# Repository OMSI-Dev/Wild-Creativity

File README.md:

# Flea Electronics Details
## Theory of Operation
Basic gameplay is three targets that are activated by IR sensors. The IR sensor detects when a ball is passing through the hole and triggers a sound effect and a lighting effect. After all three targets are hit within the games time limit a win sequence is activated and a win sound triggers. The game goes dark for five seconds and begins the attractor sequence. 

## Updating software

The software is built using platform.io. You can use Arduino IDE by copying the src folder and renaming it to Helmet and renaming the main.cpp file to ‘Helmet.ino’. This will allow you to use Arduino to make modifications. You will need to install any missing libraries through the Arduino Library manager.

## Project File Organization

	docs : documentation and pictures
	src : source code
	eagle : pcb files
	examples_tests : N/A
	readme.md : basic project info its the file you are reading
	resources:Flea BOM.xls
	
	some other directories are used by platformio and vscode

#### Hardware

**Phoenix connectors:**

2-pin: (4 qty)

3-pin: (3 qty)

4-pin: (2 qty)

6-pin: (1 qty)

Various Components:

    1.WS2811 daisychain lights
    2.5V PSU
    3.IR sensors

## Audio
A WAV trigger is used and controlled via serial communication. Audio files are saved as 16-bit WAV files on the installed SD card.

The audio uses a naming convention of 001_Win.WAV

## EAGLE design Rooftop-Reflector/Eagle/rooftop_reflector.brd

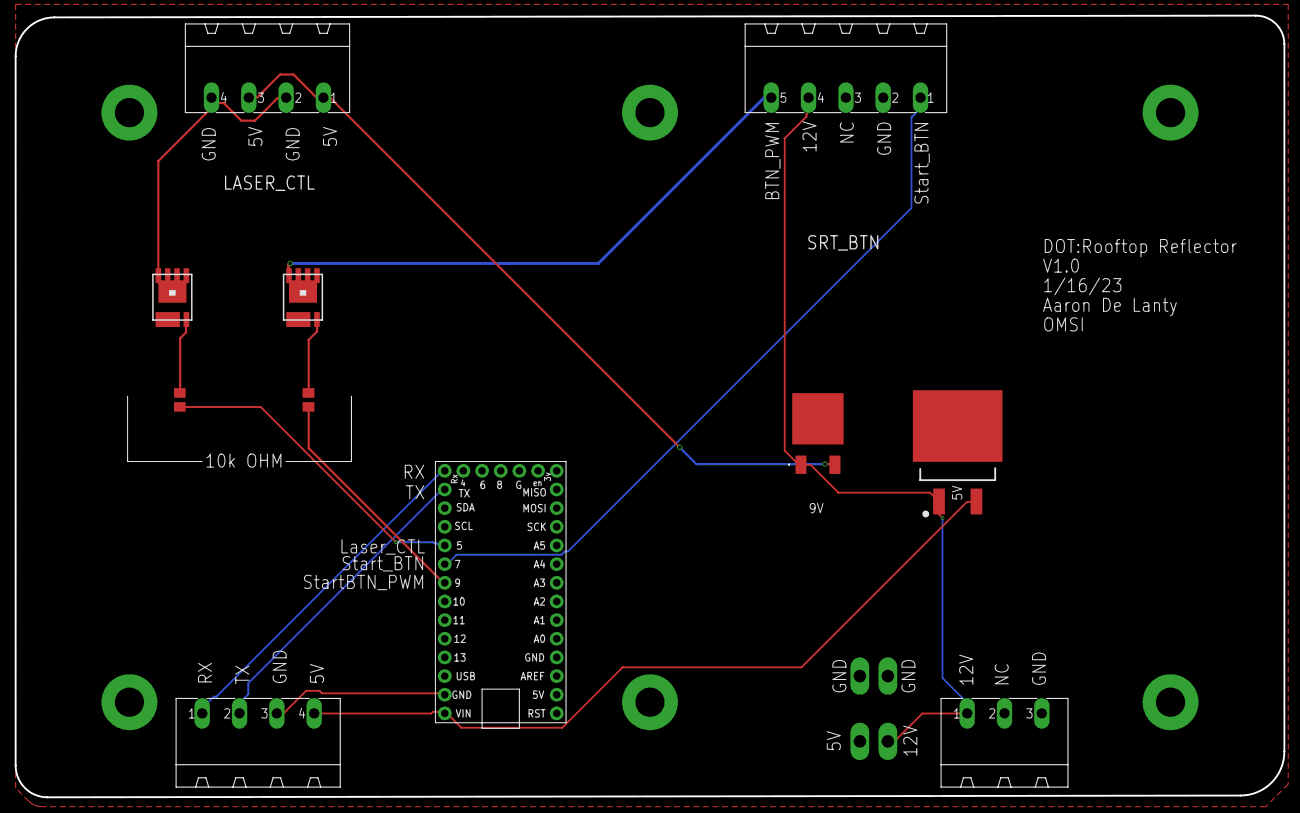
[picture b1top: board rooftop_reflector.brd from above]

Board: 2 copper layers, 172.7 x 106.4 mm, 19 parts (0 on the bottom side), 14 nets.

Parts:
5V: L7805ABD2T-TR; D2PAK-STB35NF10T4
9V: BA17809FP-E2; BA17809FPE2
10K1, 10K3: M0805
12VIN: MSTBA3
LASER_CTL: MSTBA4
Q1, Q4: MOSFET-NCH; SO-8_POWER_PAK
S1, S2, S3, S4, S6, S8: STANDOFF_ELECTRICAL5-32; STANDOFF_ELECTRICAL_5_32
SRT_BTN: MSTBA5
TP1, TP2: PTR2; P2-38-17
U1: ADAFRUIT_LEONARDO; ADAFRUIT_LENOARDO
X1: MSTBA4

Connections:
5V: 5V.3, U1.VIN, X1.4
9V: 9V.3, LASER_CTL.1, LASER_CTL.3
12V: 5V.1, 9V.1, 12VIN.1, SRT_BTN.4, TP2.TP-1
D5: 10K1.2, U1.D5
D9: 10K3.2, U1.D9
GND: 5V.4, 9V.2, 12VIN.3, Q1.S, Q4.S, S1.P1, S2.P1, S3.P1, S4.P1, S6.P1, S8.P1, SRT_BTN.2, TP1.TP-1, U1.GND@0
LZR_CTL: LASER_CTL.2, LASER_CTL.4, Q1.D1
unnamed: SRT_BTN.1, U1.D7
unnamed: 10K1.1, Q1.G
unnamed: U1.TX, X1.2
unnamed: U1.RX, X1.1
unnamed: U1.GND@2, X1.3
unnamed: 10K3.1, Q4.G
SRT_PWM: Q4.D1, SRT_BTN.5

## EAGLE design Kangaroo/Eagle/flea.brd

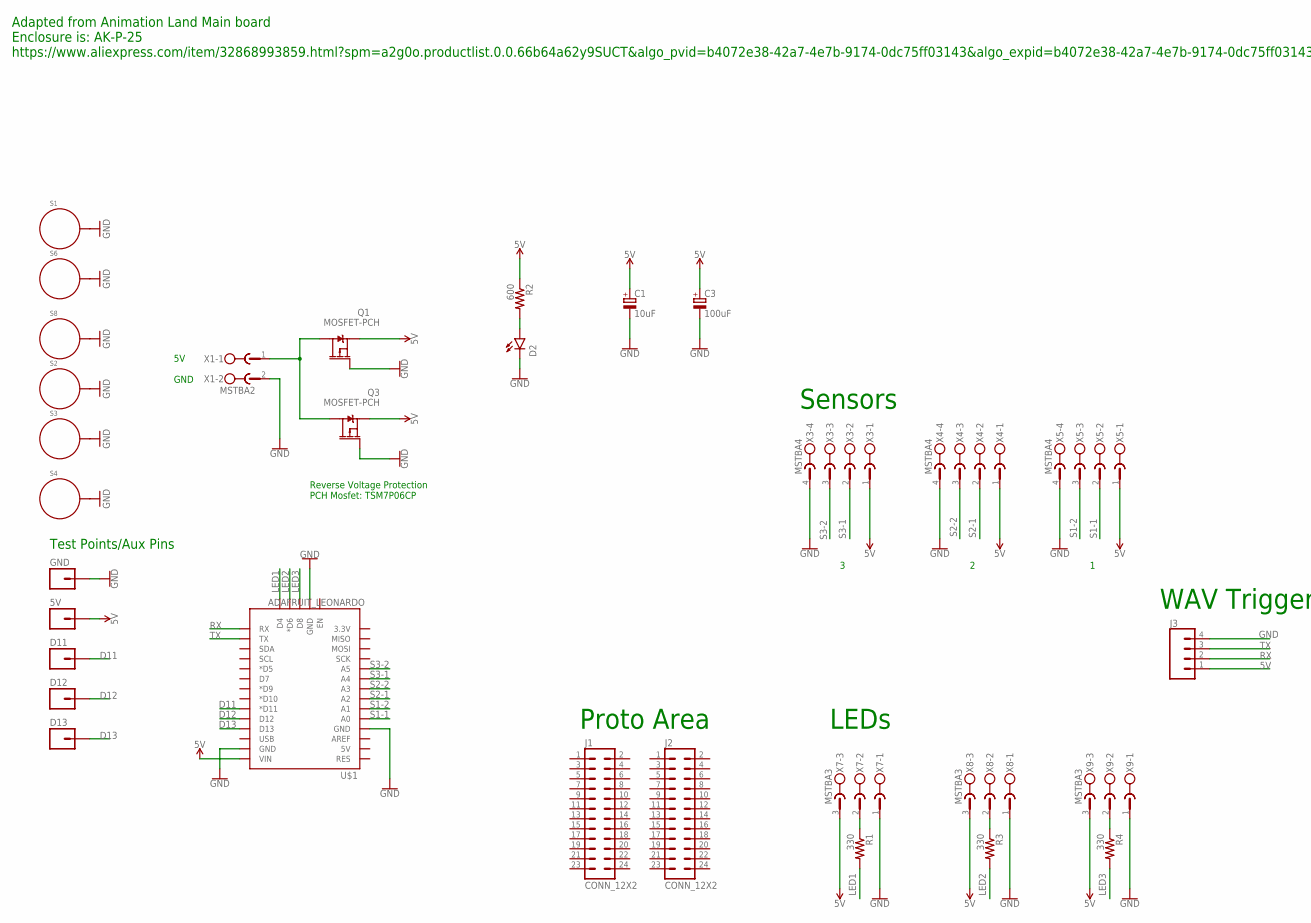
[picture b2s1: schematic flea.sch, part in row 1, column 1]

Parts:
5V: M01PTH; 1X01
C1: 10uF; E2-5
C3: 100uF; E3,5-10
D2: RED; SPARKFUN-LED_LED-1206
D11, D12, D13: M01PTH; 1X01
GND: M01PTH; 1X01
J1, J2: CONN_12X2; 2X12
J3: CONN_043.5MM_RA; 1X04_3.5MM_RA
Q1, Q3: MOSFET-PCH; DPAK
R1, R3, R4: 330; R0805
R2: 600; R0805
S1, S2, S3, S4, S6, S8: STANDOFF_ELECTRICAL5-32; STANDOFF_ELECTRICAL_5_32
U$1: ADAFRUIT_LEONARDO; ADAFRUIT_LENOARDO
X1: MSTBA2
X3, X4, X5: MSTBA4
X7, X8, X9: MSTBA3

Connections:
5V: 5V.1, C1.+, C3.+, J3.1, Q1.3 (S), Q3.3 (S), R2.1, U$1.VIN, X3.1, X4.1, X5.1, X7.3, X8.3, X9.3
D11: D11.1, U$1.D11 (*D11)
D12: D12.1, U$1.D12
D13: D13.1, U$1.D13
GND: C1.-, C3.-, D2.C, GND.1, J3.4, Q1.1 (G), Q3.1 (G), S1.P1, S2.P1, S3.P1, S4.P1, S6.P1, S8.P1, U$1.GND@0 (GND), U$1.GND@1 (GND), U$1.GND@2 (GND), X1.2, X3.4, X4.4, X5.4, X7.1, X8.1, X9.1
LED1: R1.2, U$1.D4
LED2: R3.2, U$1.D6 (*D6)
LED3: R4.2, U$1.D8
unnamed: D2.A, R2.2
unnamed: R1.1, X7.2
unnamed: R3.1, X8.2
unnamed: R4.1, X9.2
unnamed: Q1.4 (D), Q3.4 (D), X1.1
RX: J3.2, U$1.RX
S1-1: U$1.A0, X5.2
S1-2: U$1.A1, X5.3
S2-1: U$1.A2, X4.2
S2-2: U$1.A3, X4.3
S3-1: U$1.A4, X3.2
S3-2: U$1.A5, X3.3
TX: J3.3, U$1.TX

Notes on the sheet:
Adapted from Animation Land Main board Enclosure is: AK-P-25 https://www.aliexpress.com/item/32868993859.html?spm=a2g0o.productlist.0.0.66b64a62y9SUCT&algo_pvid=b4072e38-42a7-4e7b-9174-0dc75ff03143&algo_expid=b4072e38-42a7-4e7b-9174-0dc75ff03143-1&btsid=0ab6f82415815303906962744e020c&ws_ab_test=sea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
Reverse Voltage Protection PCH Mosfet: TSM7P06CP
5V GND
Proto Area
Test Points/Aux Pins
LEDs
Sensors
WAV Trigger

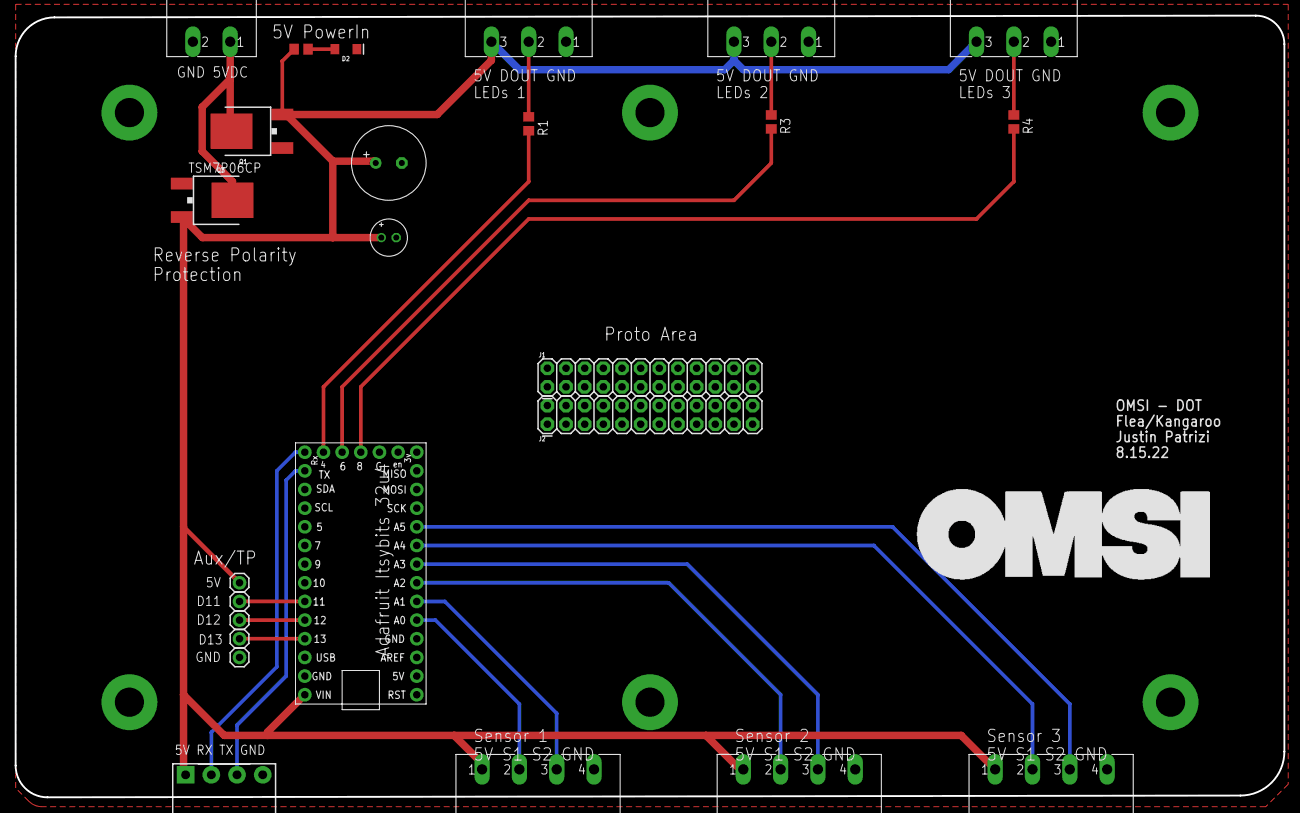
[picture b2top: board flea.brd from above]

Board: 2 copper layers, 172.7 x 106.4 mm, 31 parts (0 on the bottom side), 21 nets.

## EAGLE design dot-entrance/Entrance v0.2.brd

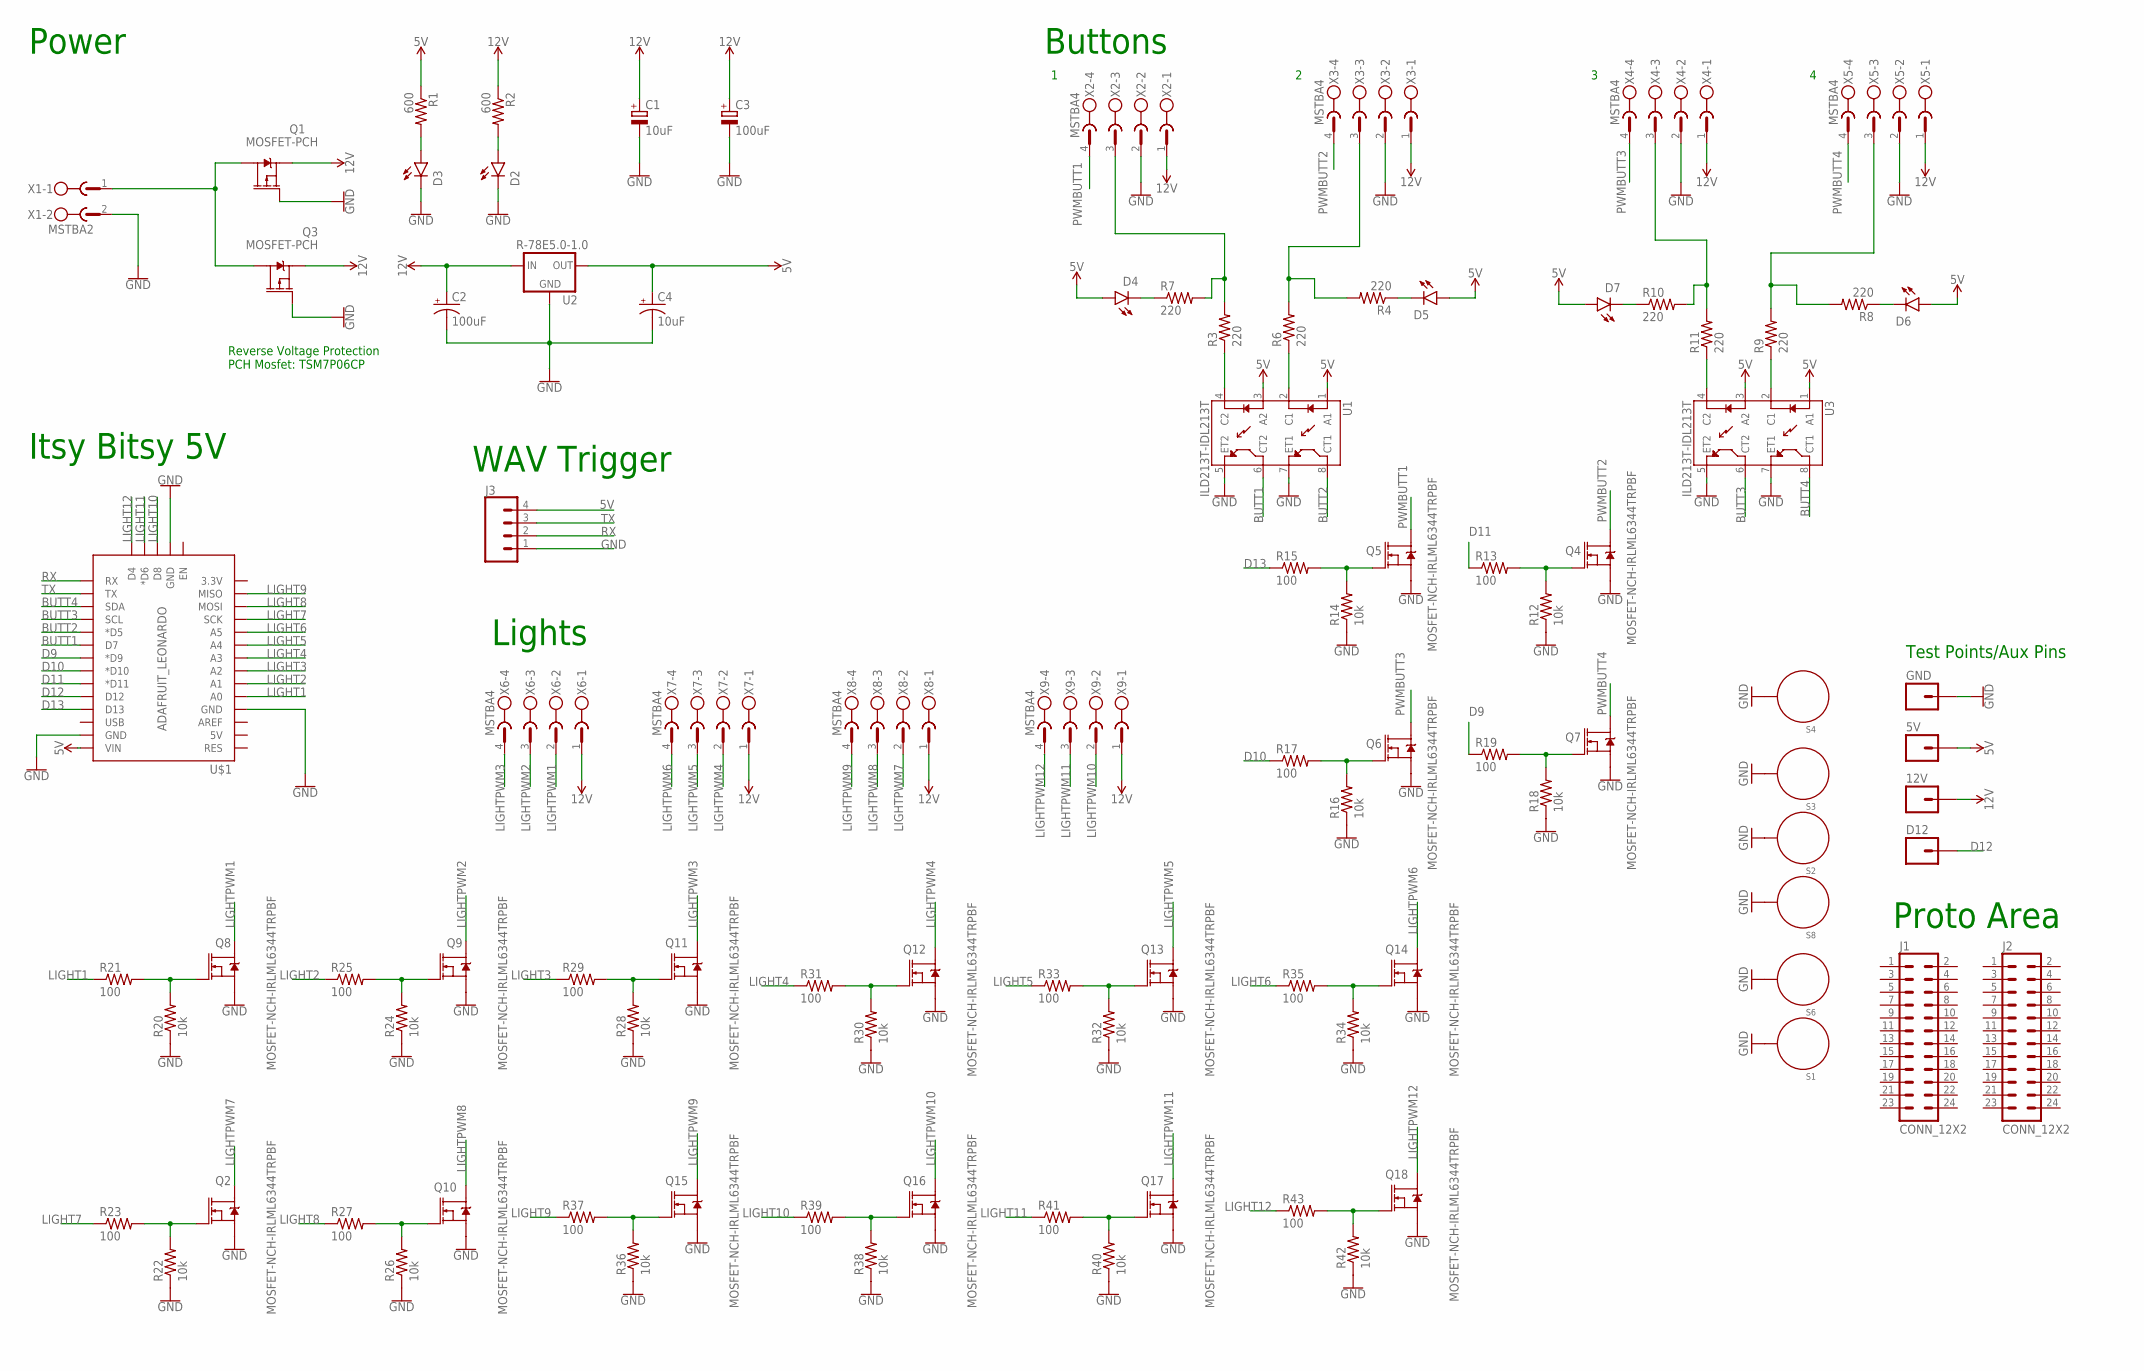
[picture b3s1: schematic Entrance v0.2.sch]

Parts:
5V, 12V: M01PTH; 1X01
C1: 10uF; E2-5
C2: 100uF; CPOL-RADIAL-2.5MM-6.5MM
C3: 100uF; E3,5-10
C4: 10uF; CPOL-RADIAL-2.5MM-5MM-KIT
D2, D3: RED; SPARKFUN-LED_LED-1206
D4, D5, D6, D7: RED; LED-1206
D12: M01PTH; 1X01
GND: M01PTH; 1X01
J1, J2: CONN_12X2; 2X12
J3: CONN_043.5MM_RA; 1X04_3.5MM_RA
Q1, Q3: MOSFET-PCH; DPAK@1
Q2, Q4, Q5, Q6, Q7, Q8, Q9, Q10, Q11, Q12, Q13, Q14, Q15, Q16, Q17, Q18: MOSFET-NCH-IRLML6344TRPBF; SOT23-3
R1, R2: 600; R0805
R3, R4, R6, R7, R8, R9, R10, R11: 220; R0805
R12, R14, R16, R18, R20, R22, R24, R26, R28, R30, R32, R34, R36, R38, R40, R42: 10k; R0805
R13, R15, R17, R19, R21, R23, R25, R27, R29, R31, R33, R35, R37, R39, R41, R43: 100; R0805
S1, S2, S3, S4, S6, S8: STANDOFF_ELECTRICAL5-32; STANDOFF_ELECTRICAL_5_32
U1, U3: ILD213T-IDL213T; SO08@1
U2: R-78E5.0-1.0; DC-DC_CONVERTER_78XX
U$1: ADAFRUIT_LEONARDO; ADAFRUIT_LENOARDO
X1: MSTBA2
X2, X3, X4, X5, X6, X7, X8, X9: MSTBA4

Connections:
5V: 5V.1, C4.1 (+), D4.A, D5.A, D6.A, D7.A, J3.4, R1.1, U1.1 (A1), U1.3 (A2), U2.VOUT (OUT), U3.1 (A1), U3.3 (A2), U$1.VIN
12V: 12V.1, C1.+, C2.1 (+), C3.+, Q1.3 (S), Q3.3 (S), R2.1, U2.VIN (IN), X2.1, X3.1, X4.1, X5.1, X6.1, X7.1, X8.1, X9.1
BUTT1: U1.6 (CT2), U$1.D7
BUTT2: U1.8 (CT1), U$1.D5 (*D5)
BUTT3: U3.6 (CT2), U$1.SCL
BUTT4: U3.8 (CT1), U$1.SDA
D9: R19.1, U$1.D9 (*D9)
D10: R17.1, U$1.D10 (*D10)
D11: R13.1, U$1.D11 (*D11)
D12: D12.1, U$1.D12
D13: R15.1, U$1.D13
GND: C1.-, C2.2 (-), C3.-, C4.2 (-), D2.C, D3.C, GND.1, J3.1, Q1.1 (G), Q2.2 (S), Q3.1 (G), Q4.2 (S), Q5.2 (S), Q6.2 (S), Q7.2 (S), Q8.2 (S), Q9.2 (S), Q10.2 (S), Q11.2 (S), Q12.2 (S), Q13.2 (S), Q14.2 (S), Q15.2 (S), Q16.2 (S), Q17.2 (S), Q18.2 (S), R12.1, R14.1, R16.1, R18.1, R20.1, R22.1, R24.1, R26.1, R28.1, R30.1, R32.1, R34.1, R36.1, R38.1, R40.1, R42.1, S1.P1, S2.P1, S3.P1, S4.P1, S6.P1, S8.P1, U1.5 (ET2), U1.7 (ET1), U2.GND, U3.5 (ET2), U3.7 (ET1), U$1.GND@0 (GND), U$1.GND@1 (GND), U$1.GND@2 (GND), X1.2, X2.2, X3.2, X4.2, X5.2
LIGHT1: R21.1, U$1.A0
LIGHT2: R25.1, U$1.A1
LIGHT3: R29.1, U$1.A2
LIGHT4: R31.1, U$1.A3
LIGHT5: R33.1, U$1.A4
LIGHT6: R35.1, U$1.A5
LIGHT7: R23.1, U$1.SCK
LIGHT8: R27.1, U$1.MOSI
LIGHT9: R37.1, U$1.MISO
LIGHT10: R39.1, U$1.D8
LIGHT11: R41.1, U$1.D6 (*D6)
LIGHT12: R43.1, U$1.D4
LIGHTPWM1: Q8.3 (D), X6.2
LIGHTPWM2: Q9.3 (D), X6.3
LIGHTPWM3: Q11.3 (D), X6.4
LIGHTPWM4: Q12.3 (D), X7.2
LIGHTPWM5: Q13.3 (D), X7.3
LIGHTPWM6: Q14.3 (D), X7.4
LIGHTPWM7: Q2.3 (D), X8.2
LIGHTPWM8: Q10.3 (D), X8.3
LIGHTPWM9: Q15.3 (D), X8.4
LIGHTPWM10: Q16.3 (D), X9.2
LIGHTPWM11: Q17.3 (D), X9.3
LIGHTPWM12: Q18.3 (D), X9.4
unnamed: R3.1, U1.4 (C2)
unnamed: D2.A, R2.2
unnamed: D6.C, R8.1
unnamed: D3.A, R1.2
unnamed: D4.C, R7.1
unnamed: D5.C, R4.1
unnamed: R3.2, R7.2, X2.3
unnamed: R6.1, U1.2 (C1)
unnamed: R4.2, R6.2, X3.3
unnamed: R9.1, U3.2 (C1)
unnamed: R8.2, R9.2, X5.3
unnamed: D7.C, R10.1
unnamed: R10.2, R11.2, X4.3
unnamed: R11.1, U3.4 (C2)
unnamed: Q5.1 (G), R14.2, R15.2
unnamed: Q6.1 (G), R16.2, R17.2
unnamed: Q7.1 (G), R18.2, R19.2
unnamed: Q1.4 (D), Q3.4 (D), X1.1
unnamed: Q8.1 (G), R20.2, R21.2
unnamed: Q2.1 (G), R22.2, R23.2
unnamed: Q9.1 (G), R24.2, R25.2
unnamed: Q10.1 (G), R26.2, R27.2
unnamed: Q11.1 (G), R28.2, R29.2
unnamed: Q4.1 (G), R12.2, R13.2
unnamed: Q12.1 (G), R30.2, R31.2
unnamed: Q13.1 (G), R32.2, R33.2
unnamed: Q14.1 (G), R34.2, R35.2
unnamed: Q15.1 (G), R36.2, R37.2
unnamed: Q16.1 (G), R38.2, R39.2
unnamed: Q17.1 (G), R40.2, R41.2
unnamed: Q18.1 (G), R42.2, R43.2
PWMBUTT1: Q5.3 (D), X2.4
PWMBUTT2: Q4.3 (D), X3.4
PWMBUTT3: Q6.3 (D), X4.4
PWMBUTT4: Q7.3 (D), X5.4
RX: J3.2, U$1.RX
TX: J3.3, U$1.TX

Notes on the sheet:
Reverse Voltage Protection PCH Mosfet: TSM7P06CP
Proto Area
Test Points/Aux Pins
Lights
Buttons
WAV Trigger
Itsy Bitsy 5V
Power

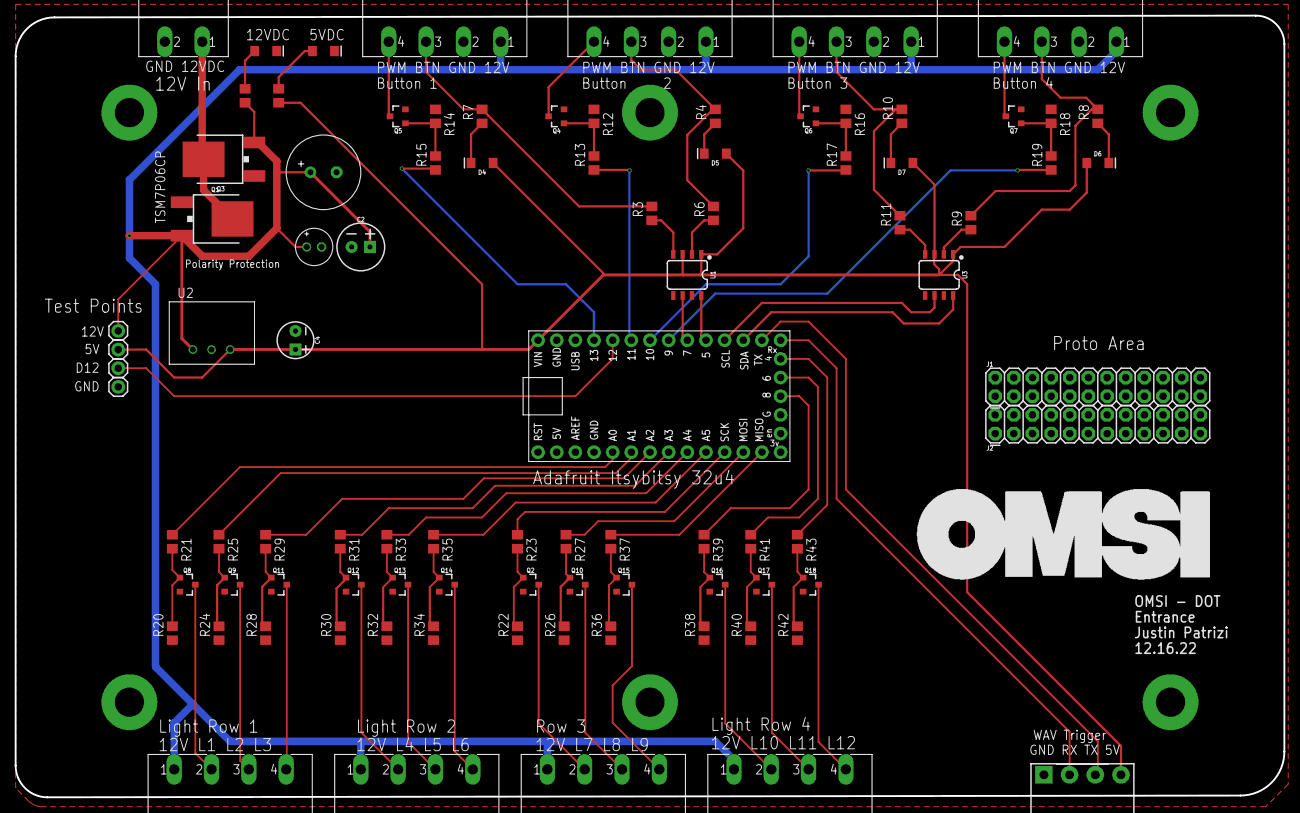
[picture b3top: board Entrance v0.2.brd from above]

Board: 2 copper layers, 172.7 x 106.4 mm, 96 parts (0 on the bottom side), 73 nets.

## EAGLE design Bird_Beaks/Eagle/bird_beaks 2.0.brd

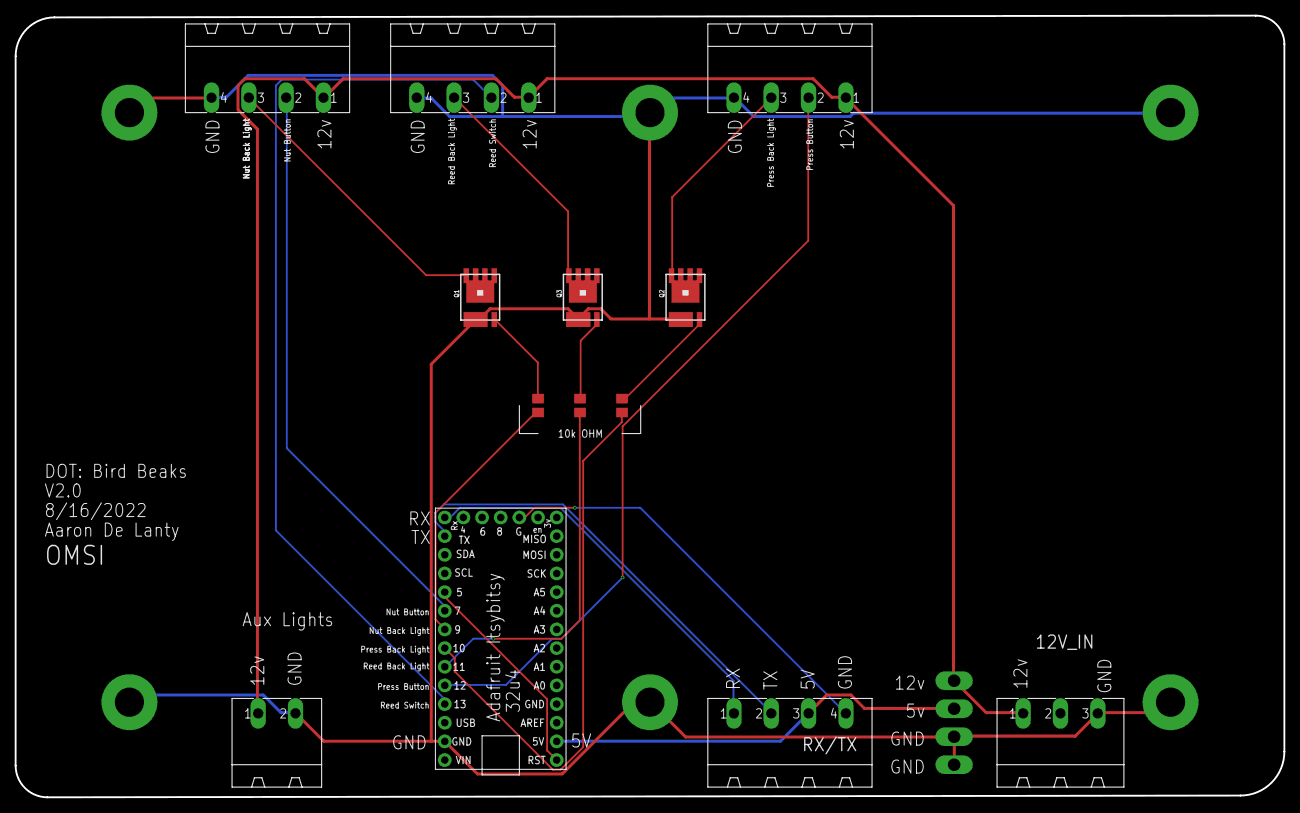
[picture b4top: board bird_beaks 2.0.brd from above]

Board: 2 copper layers, 172.7 x 106.4 mm, 21 parts (0 on the bottom side), 19 nets.

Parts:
10K, 10K1, 10K2: M0805
12V_IN: MSTBA3
Q1, Q2, Q3: MOSFET-NCH; SO-8_POWER_PAK
RX/TX: MSTBA4
S1, S2, S3, S4, S6, S8: STANDOFF_ELECTRICAL5-32; STANDOFF_ELECTRICAL_5_32
TP1, TP2: PTR2; P2-38-17
U1: ITSYBITSY_5V; ADAFRUIT_LENOARDO
X1, X2, X3: MSTBA4
X4: MSTBA2

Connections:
5V: RX/TX.3, TP2.TP-1, U1.5V
12V: 12V_IN.1, TP2.TP-2, X1.1, X2.1, X3.1, X4.1
D7: U1.D7, X1.2
D9: 10K.2, U1.D9
D10: 10K1.2, U1.D10
D11: 10K2.2, U1.D11
D12: U1.D12, X2.2
D13: U1.D13, X3.2
GND: 12V_IN.3, Q1.S, Q2.S, Q3.S, S1.P1, S2.P1, S3.P1, S4.P1, S6.P1, S8.P1, TP1.TP-1, TP1.TP-2, U1.GND@2, X1.4, X2.4, X3.4, X4.2
unnamed: 10K2.1, Q3.G
unnamed: 10K.1, Q1.G
unnamed: U1.D5, U1.RES
unnamed: Q1.D1, X1.3
unnamed: 10K1.1, Q2.G
unnamed: RX/TX.2, U1.TX
unnamed: Q2.D1, X2.3
unnamed: RX/TX.4, U1.GND@1
unnamed: RX/TX.1, U1.RX
unnamed: Q3.D1, X3.3

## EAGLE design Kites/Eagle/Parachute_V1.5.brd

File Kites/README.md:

# Kites Electronics Details
### Theory of Operation
The basic operation of kites is a processing sketch and a uController controlling two blower fans and reading a veneer force sensor. The uController has a start and stop button connected to control the gameplay game state. 

When the start button is pressed it sends a signal to processing to activate the data output screen. This then pulls down the signal to start the fans connected to the relay-controlled powerstrip. The uController reads the incoming sensor data and sends it over serial signal packets with an LF to end the packet. Processing takes the data and maps it to a -35 to 35 value that determines the position of the dial gauge's rotation on the screen. This data also updates the battery charging levels relative to the gauge. After the game timeout, it outputs a results screen that translates the gauge to the number of minutes to charge a battery. 

The processing app handles the game timing once it gets the signal from the uController to start the game. It will also cut the game off sooner if the stop button is pushed during gameplay. When it receives the signal to start it does a countdown to start the game while the fans spin up. The game plays for the duration of the timer while updating the visual feedback elements. After the timer finishes the game shows results and then sends a signal to the uController to reset and turn off the fans. It then switches back to the attractor video. 

### Updating software

The software is built using platform.io. You can use Arduino IDE by copying the src folder and renaming it to Kites and renaming the main.cpp file to ‘Helmet.ino’. This will allow you to use Arduino to make modifications. You will need to install any missing libraries through the Arduino Library manager.

### Project File Organization

docs : documentation and pictures 
src : source code 
eagle : pcb files 
examples_tests : N/A 
processing: location of computer app
 processing/data: assets used for the processing app 
readme.md : basic project info its the file you are reading 
resources:Kites BOM.xls 
some other directories are used by platformio and vscode

Hardware

Phoenix connectors:

3-pin: (1 qty) 

    1. 12V IN
    
4-pin: (2 qty) 

    1. Fan Power

 8-pin: (1 qty) 

    1. Start Light
    2. Stop Light
    3. Start Btn
    4. Stop Btn

Various components

    2 mosfets (SMD 7460AAW44K) 
    2 10K SMS Resistors
    32U4 - 5v itsyBitsy
    Vernier Sensor
    12V PSU 
    5V across USB
    
### Audio

They are Mp3 files stored /data/sound/ and can be updated simply by following the naming scheme and replacing old files. It is recommended to make a backup before replacing any files. Capitalization matters.

##### Naming scheme:

    Failure: red.mp3 
    Average: orange.mp3 
    Success: green.mp3
    Countdown: countdown.mp3
    Countdown Start: countdownStart.mp3

### Images/video
The images are saved as PNG and the video is MP4, both are stored /data/images. by following the naming scheme and replacing old files. It is recommended to make a backup before replacing any files. Capitalization matters.

##### Naming scheme:

    Battery Red: battR.png 
    Battery Yellow: battY.png 
    Battery Green: battG.png
    Phone Red: rPhone.png 
    Phone Yellow: yPhone.png 
    Phone Green: gPhone.png
    Results Phone: results.png 
    Gauge Red: rGauge.png
    Gauge Yellow: yGauge.png
    Gauge Green: gGauge.png
    Game Timer: activeTimer.png
    Count in Timer: countdownTimer.png
    Gauge Dial: dail.png
    results splash: splash.png
    Video: attractor.mp4

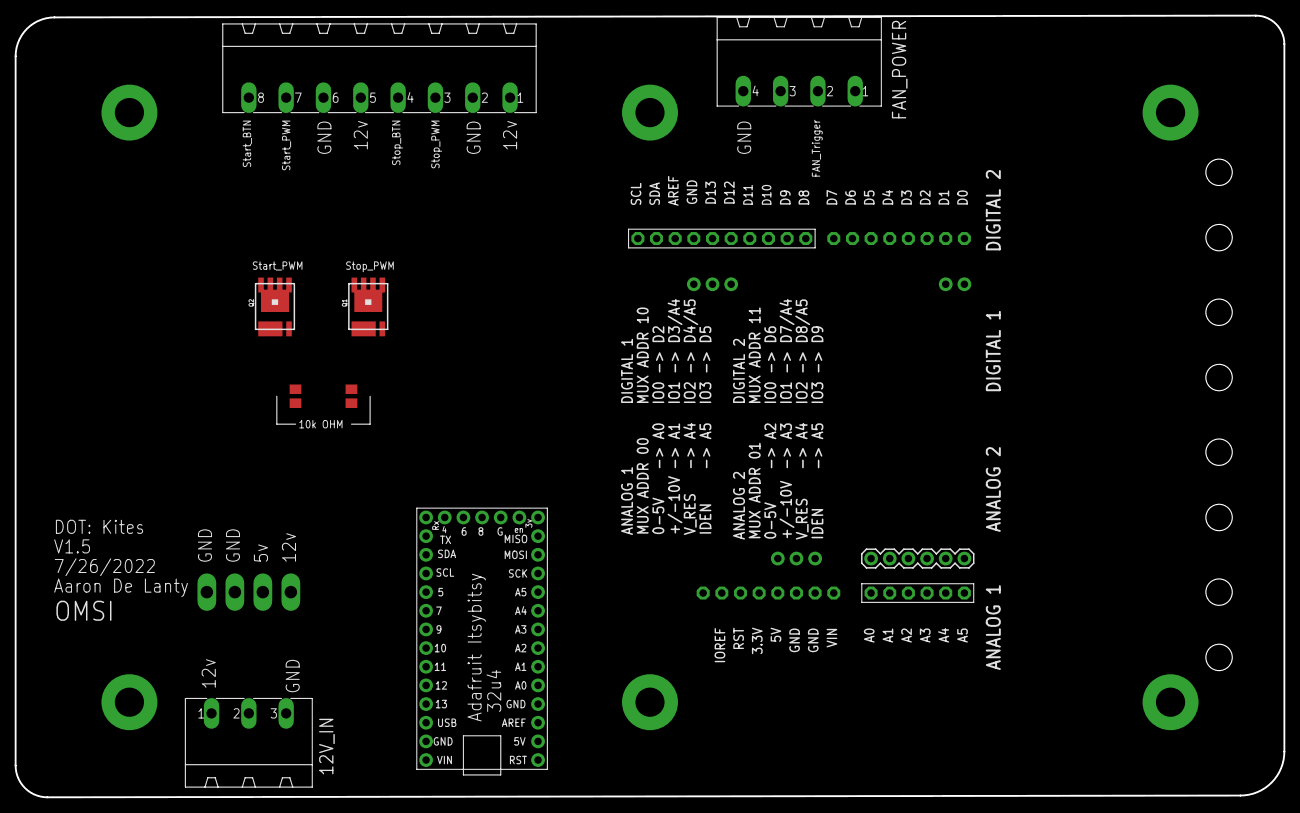
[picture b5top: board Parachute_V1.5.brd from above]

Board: 2 copper layers, 172.7 x 106.4 mm, 24 parts (0 on the bottom side), 31 nets, no tracks yet.

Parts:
10K, 10K1: M0805
12V_IN: MSTBA3
FAN_POWER: MSTBA4
JP1, JP2: 1X08-CLEANBIG
JP3: 1X06-BIG
JP9, JP10: 1X03_NO_SILK
JP11: M021X02_NO_SILK; 1X02_NO_SILK
JP12: Male; 1X06
Q1, Q2: MOSFET-NCH; SO-8_POWER_PAK
S1, S2, S3, S4, S6, S8: STANDOFF_ELECTRICAL5-32; STANDOFF_ELECTRICAL_5_32
TP1, TP2: PTR2; P2-38-17
U1: ITSYBITSY_5V; ADAFRUIT_LENOARDO
U$1: PINHD-1X10; 1X10-BIG
X1: MSTBA8

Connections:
5V: JP2.4, JP9.1, TP2.TP-1, U1.5V
12V: 12V_IN.1, TP2.TP-2, X1.1, X1.5
A3: JP3.4, JP12.3, U1.A3
GND: 12V_IN.3, FAN_POWER.4, JP2.2, JP2.3, JP9.2, JP9.3, JP10.3, Q1.S, Q2.S, S1.P1, S2.P1, S3.P1, S4.P1, S6.P1, S8.P1, TP1.TP-1, TP1.TP-2, U1.GND@2, U$1.7, X1.2, X1.6
unnamed: Q2.D1, X1.7
unnamed: Q1.D1, X1.3
unnamed: JP1.1, JP11.2, U1.RX
unnamed: U1.D8, U$1.1
unnamed: JP1.2, JP11.1, U1.TX
unnamed: U1.AREF, U$1.8
unnamed: 10K.1, Q1.G
unnamed: JP3.1, JP12.6, U1.A0
unnamed: 10K1.1, Q2.G
unnamed: JP3.2, JP12.5, U1.A1
unnamed: JP3.3, JP12.4, U1.A2
unnamed: JP3.5, JP12.2, U1.A4
unnamed: JP3.6, JP12.1, U1.A5
unnamed: JP10.2, U1.D12, U$1.6
unnamed: JP1.3, U1.SDA, U$1.9
unnamed: JP1.4, U1.SCL, U$1.10
unnamed: JP10.1, U1.D13, U$1.5
unnamed: JP1.6, U1.D5, X1.8
unnamed: JP1.7, U1.D6
unnamed: JP1.8, U1.D7, X1.4
unnamed: JP1.5, U1.D4
unnamed: JP2.6, U1.RES
unnamed: JP2.5, U1.3V
unnamed: FAN_POWER.2, U1.D9, U$1.2
unnamed: 10K1.2, U1.D10, U$1.3
unnamed: 10K.2, U1.D11, U$1.4
unnamed: JP2.1, U1.VIN

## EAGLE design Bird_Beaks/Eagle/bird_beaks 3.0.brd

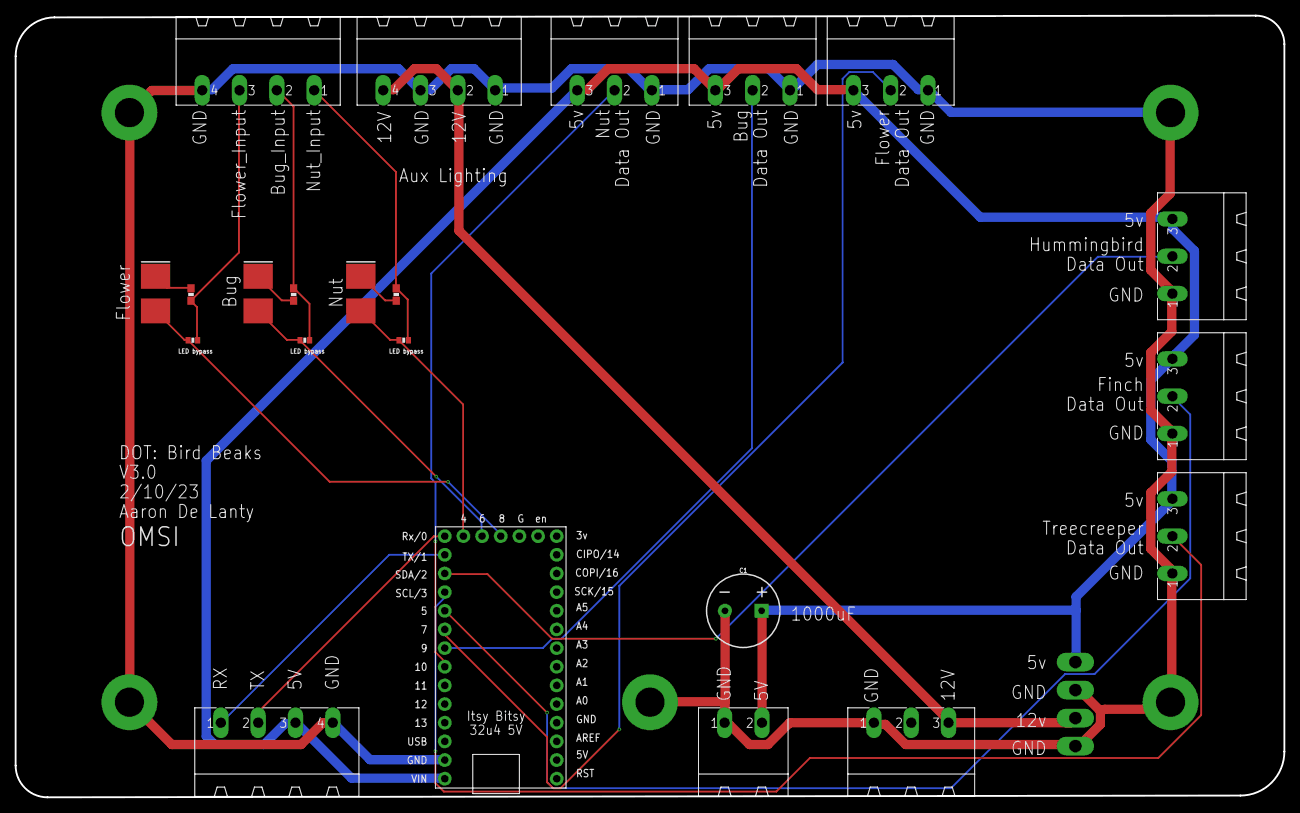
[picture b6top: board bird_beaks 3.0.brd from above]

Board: 2 copper layers, 172.7 x 106.4 mm, 29 parts (0 on the bottom side), 20 nets.

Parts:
C1: 1mf; CAP_RADIAL_10MM
D1, D2, D3: SPARKFUN-LED_SFH4641SHORT; SPARKFUN-LED_SFH4641-SHORT
R1, R2, R3: SMD_RESISTOR__0603
R4, R5, R6: SMD_RESISTOR_0402
S1, S3, S4, S6, S8: STANDOFF_ELECTRICAL5-32; STANDOFF_ELECTRICAL_5_32
TP1, TP2: PTR2; P2-38-17
U1: ADAFRUIT_ITSYBITSY_5V; ADAFRUIT_ITSYBITSY
X1, X2, X3, X7, X8, X9, X10: PHOENIX_508_3PIN
X4: PHOENIX_508_2PIN
X5, X6, X11: PHOENIX_508_4PIN

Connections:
5V: C1.+, TP2.TP-2, U1.VIN, X1.3, X2.3, X3.3, X4.2, X5.3, X7.3, X8.3, X9.3
12V: TP1.TP-2, X10.3, X11.2, X11.4
BUG_INPUT: R2.2, R4.2, X6.2
BUG_OUTPUT: U1.D9, X3.2
FINCH_OUTPUT: U1.D5, X2.2
FLOWER_INPUT: R1.2, R6.2, X6.3
FLOWER_OUTPUT: U1.D7, X8.2
GND: C1.-, S1.P1, S3.P1, S4.P1, S6.P1, S8.P1, TP1.TP-1, TP2.TP-1, U1.GND@2, X1.1, X2.1, X3.1, X4.1, X5.4, X6.4, X7.1, X8.1, X9.1, X10.1, X11.1, X11.3
HUMMINGBIRD_OUTPUT: U1.SDA, X9.2
unnamed: D3.C, R3.1
unnamed: D2.C, R2.1
unnamed: D1.C, R1.1
unnamed: D1.A, R6.1, U1.D8
unnamed: D2.A, R4.1, U1.D6
unnamed: D3.A, R5.1, U1.D4
unnamed: U1.TX, X5.1
unnamed: U1.RX, X5.2
NUT_INPUT: R3.2, R5.2, X6.1
NUT_OUTPUT: U1.D10, X1.2
TREECREEPER_OUTPUT: U1.SCL, X7.2

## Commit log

2022-09-12 init
2022-09-12 added image assests
2022-09-12 documentation
2022-09-14 Fixed pinout on board causing StopbtnPWN to ground Updated code to have proper breathing animation for each button
2022-09-19 added Readme
2022-09-19 Create Helmet
2022-09-19 Added Readme to main
2022-09-19 fixed naming scheme for dial
2022-09-19 Updated kites CAM for circuit manufacturing
2022-09-19 Updated CAM for circuit manufacturing
2022-09-23 various fixes
2022-10-03 minor change
2022-10-03 init
    Recreated repository due to issues with Google Drive. Former Repository is now archived for historical records only.
2022-10-17 added extra pin to control fan
2022-11-11 Calibration
    Added Calibration routine, current implementation is not production ready. Waiting on new board to add calibration button & to save to EEPROM. This is intended to be ran during first setup at new ven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
2022-11-15 Update README.md
    updated mosfet
2022-11-16 Documentation
    Started Documentation
2022-11-16 Updated repository to match most recent revisions
2022-11-16 Updated to make newest repository location
2022-11-16 added EEPROM test code
2023-01-06 Game & audio added
2023-01-06 updated values
2023-01-07 updated homing and pins
2023-01-18 adjusted image limits & data
2023-01-18 Create Bird Beaks
2023-01-18 added calibration button
2023-01-30 Updated Btn calls and added Pulse function
2023-01-30 Added MoToTimer & Pulse function
2023-01-31 removed sound pins; added pulse function & fixed calibration button
2023-01-31 added Pulse library
2023-02-03 sound updates
2023-02-03 test update
2023-02-07 reorg
2023-02-07 restructured base
2023-02-07 smol update
2023-02-08 fixed typos
2023-02-08 test push
2023-02-10 rebuild of base game
2023-02-10 fixed game restart loop
2023-02-16 added drift correction & door catch
2023-02-16 fixed bool & added double check for safety
2023-02-20 added in Serial timeout
2023-03-20 Test Fix
2023-03-23 added test Zero Calibration
2023-03-27 New tare/calibration
    Processing sends calibration signal to arduino at start to calibrate before turning on fan
2023-03-29 Clears graph on movie start.
2023-03-29 Door Safty Update
2023-03-29 reduced chart values
2023-03-29 Added logFile generation
2023-04-03 Update Helmet_drop.pde
    This should correct errors when applying to the graph. Generates a logFile. If fails 2nd attempt to update it will close the program and update the log.
2023-04-06 Exit Code Added & Eased Difficulty
2023-04-06 adjusted light delays
2023-05-05 calibration reset
    This needs to be tuned more
2023-05-12 attractor fix
2023-05-16 Moved connectors for ease of access
2023-05-19 board edits
2023-05-19 Logs from testing
2023-06-12 created function called lightupdate()
    installed FastLED library, and initialized the LED'in main, in sensor update created a function called lightupdate() that takes the sensor data from the airflow sensor outputs the color of light that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
2023-06-13 update new game mechanics
2023-06-19 added pcb files
2023-06-19 So many stupid updates
2023-06-20 graphics
2023-06-21 update graphics and zero divide issue
2023-06-21 Added delay for quick time fix
2023-06-22 Revision for output
2023-06-22 board fix
2023-06-28 update to fix graph zero
2023-06-28 Added Logging
2023-07-07 added new logfile info and error handing
2023-07-07 added light files
2023-07-07 update and org
2023-07-14 completed the attractor sequence
    fully flushed out the attractor sequence so that it will pulse on and off
2023-07-19 new sound and bug fix
2023-07-19 added try-catch to accel read
2023-07-19 updated the winsequence
    new function for win sequnce still hanging after one passthrough
2023-07-20 e-homing switch added
2023-07-21 demo mode
2023-07-24 win sequence done
    there ya go
2023-07-24 converted to minim sound library
2023-07-26 added EMA
2023-07-26 changed pin for RGB and LEDs
    here
2023-07-28 update to led chase timings
2023-07-28 updated lighiting call
2023-08-02 EMA update
2023-08-02 new light updates
    here
2023-08-25 changed the direction of lights and logic
    instead of having one array that is broken up into pointers and then manually changed we break up the large array into smaller ones and then address each one seperately
2023-08-25 studpid hammer update
2023-09-13 color correction code
2023-09-18 update 5V lead and comments
2023-09-20 final
2023-09-20 commiting
2023-09-20 clearing
2023-09-20 Orginizing
2023-09-20 archiving
2023-09-20 archive and backup
2023-10-06 updated indicator lights
2023-10-09 cleanup
2024-04-17 restructure
2024-05-27 tweaks
2024-07-15 updated pins
2024-07-15 Create Entrance v0.2.b##
2024-12-18 audio updates
2024-12-18 Recovered Bird Beaks

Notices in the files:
parts and their libraries:
SparkFun-Connectors: Licensing: Creative Commons ShareAlike 4.0 International - https://creativecommons.org/licenses/by-sa/4.0
SparkFun-Connectors: Licensing: CC v3.0 Share-Alike You are welcome to use this library for commercial purposes.
